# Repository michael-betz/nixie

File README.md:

# nixie
My exercise in OpenScad.
a HP 5245L frequency counter had to die for this ...

# Lessons learned the hard way
Murphy was strong on this one ...

  * Nixie pins are fragile and don't like too tight sockets. RIP 2 tubes ...
  * The HV5530 in a PQFP package has a different pinout than the one in a PLCC package. Fixed it with tons of botch wire :weary:
  * Didn't notice that the nixie tube datasheet shows the pinout from the bottom :unamused:. Fixed it with a lot more botch wire
  * Feel free to re-do the layout in kicad ...
  * Magnet wire insulation didn't hold up to 180 V. Killed 2 x ESP32 that way. Fixed it with conformal coating
  * Didn't keep conformal coating away from push buttons, it disabled them
  * Hole pattern between PCB and 3D print was off by ~ 3 mm due to a typo in the 3D model. Fixed it by bending the 3D printed part with a hot air gun
  * Had to cut some of the 3D printed stand-offs and the ESP32 PCB antenna to make it all fit

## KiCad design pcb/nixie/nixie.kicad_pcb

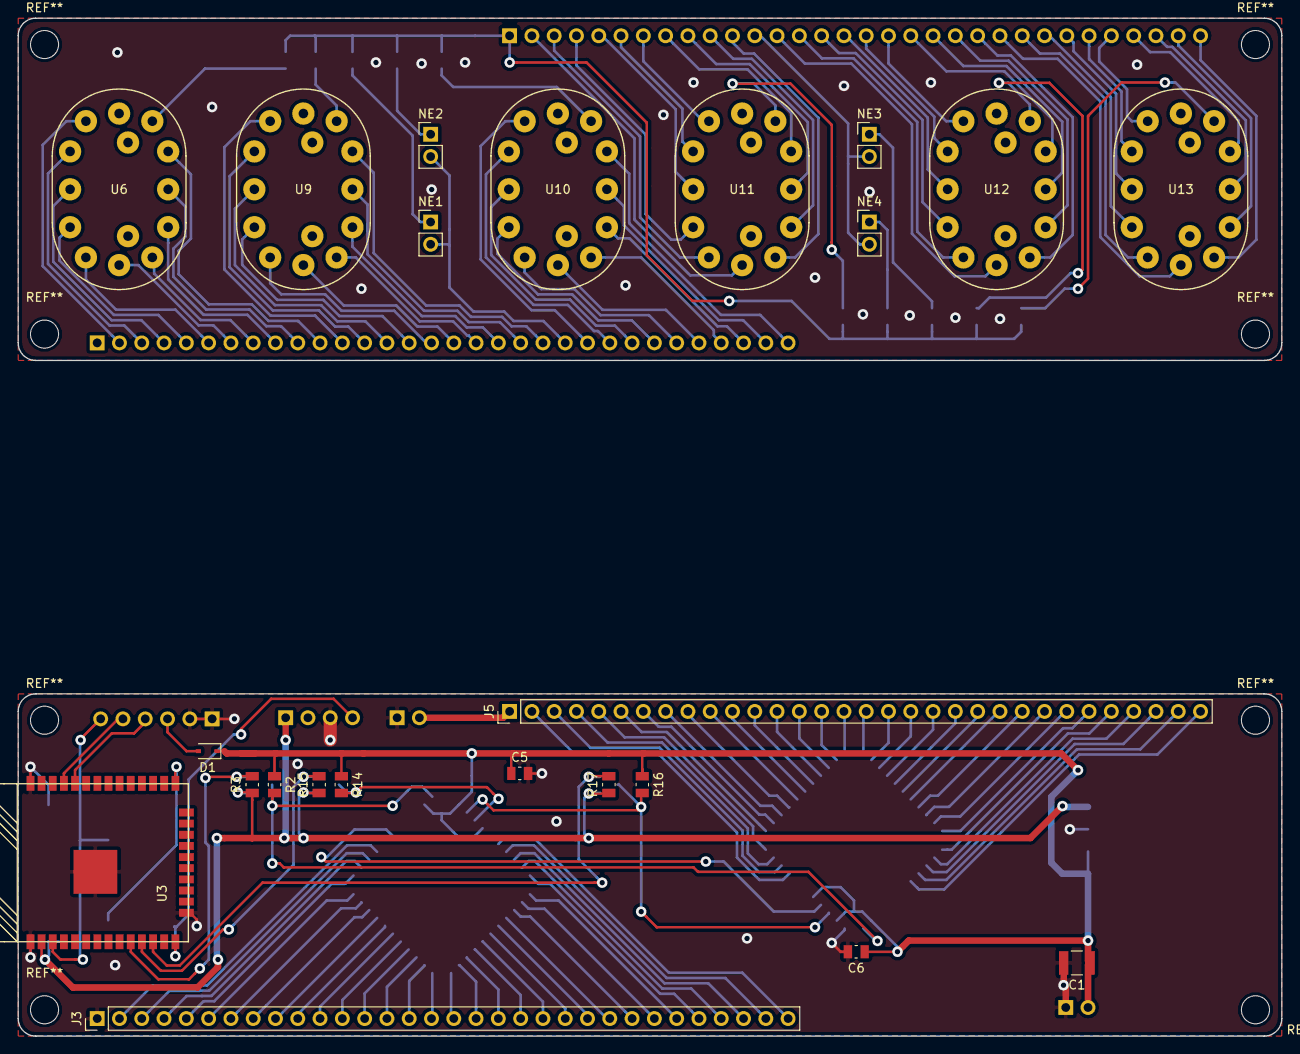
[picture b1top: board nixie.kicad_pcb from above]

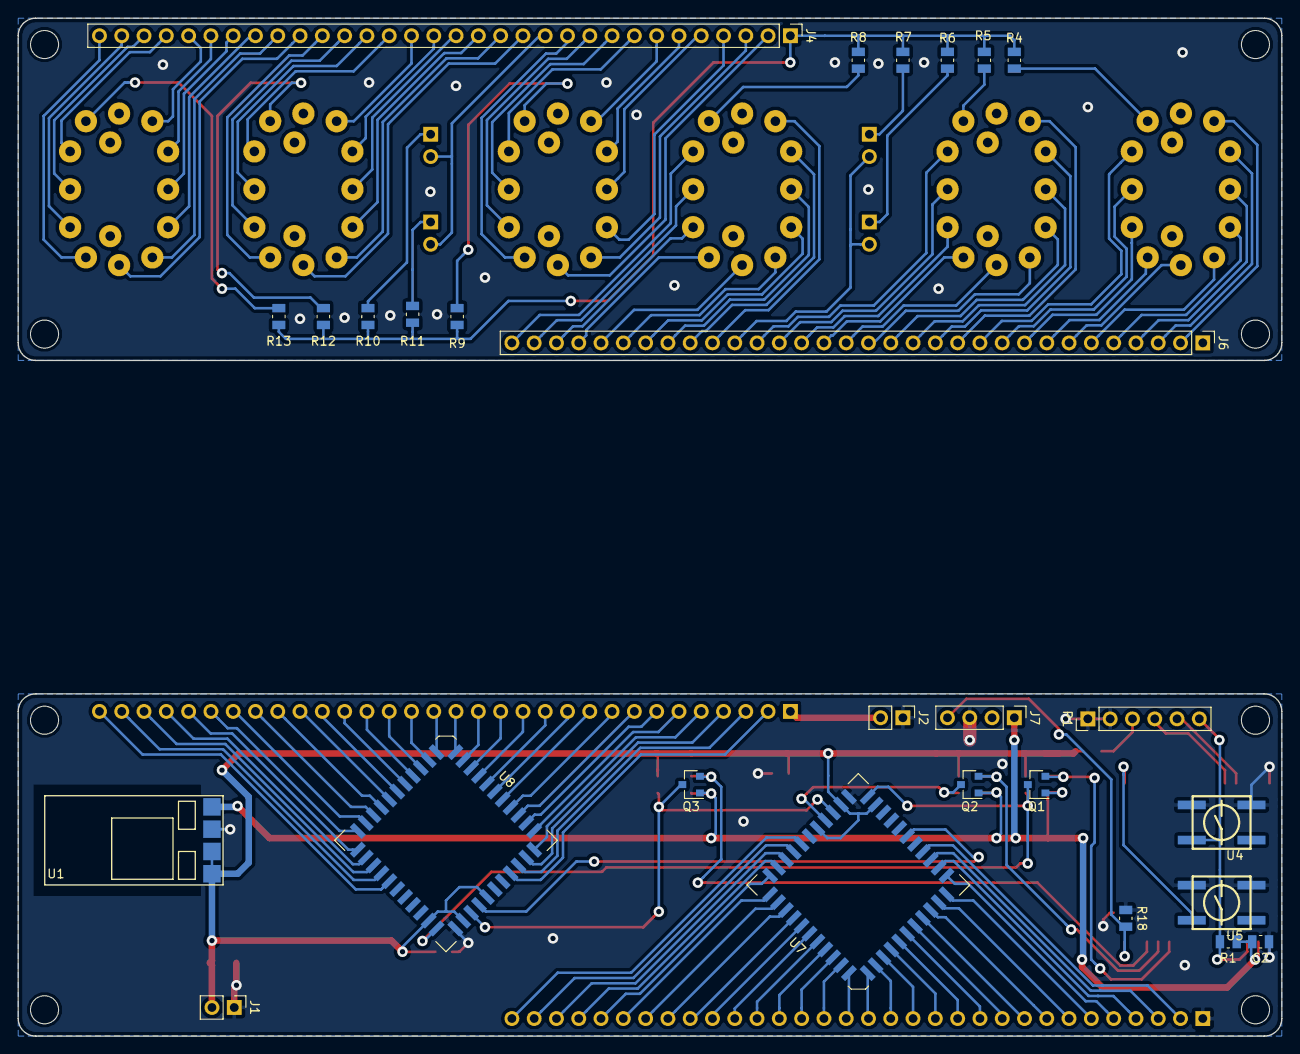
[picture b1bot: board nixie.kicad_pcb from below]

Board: 2 copper layers, 144.0 x 116.0 mm, 50 parts (27 on the bottom side), 90 nets.

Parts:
C1: 10u; C_1210_3225Metric
C2, C5, C6: 1u; C_0805_2012Metric
D1: B5819WS; D_SOD-323
J1, J2: Conn_01x02; PinHeader_1x02_P2.54mm_Vertical
J3, J4, J5, J6: Conn_01x32; PinHeader_1x32_P2.54mm_Vertical
J7: Conn_01x04; PinHeader_1x04_P2.54mm_Vertical
NE1, NE2, NE3, NE4: n; PinHeader_1x02_P2.54mm_Vertical
P1: TTL_232R_3V3; PinHeader_1x06_P2.54mm_Vertical
Q1, Q2, Q3: BSS138; SOT-23
R1: 470k; R_0805_2012Metric
R2, R3, R4, R5, R6, R7, R8, R9, R10, R11, R12, R13, R14, R15, R16, R17: 10k; R_0805_2012Metric
R18: 50R; R_0805_2012Metric
U1: DCDC_mod; ebay_dcdc
U3: ESP-WROOM-32
U4, U5: TACTILE; EVQQ2
U6, U9, U10, U11, U12, U13: nixie_8422
U7, U8: HV5530; PLCC-44

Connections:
+3V3: C2.2, J7.1, Q1.1, Q2.1, Q3.1, R1.1, R3.1, R15.1, R17.1, U1.1, U3.2
+12V: C1.1, C5.1, C6.1, D1.1, J1.2, R2.1, R14.1, R16.1, U1.3, U1.4, U7.27, U7.30, U7.33, U8.27, U8.30, U8.33
/progFlag: U3.25, U5.A, U5.A'
/rstBtn: P1.6, R1.2, U3.3, U4.A, U4.A'
/tubes/clk: Q1.3, R2.2, U7.28, U8.28
/tubes/colons_0: J5.12, J6.12, NE3.2, NE4.2, U8.2
/tubes/colons_1: J3.22, J4.22, NE1.2, NE2.2, U7.1
/tubes/dat: Q2.3, R14.2, U7.32
/tubes/n0_0: J5.29, J6.29, U8.19, U13.2
/tubes/n0_1: J5.28, J6.28, U8.18, U13.11
/tubes/n0_2: J5.27, J6.27, U8.17, U13.10
/tubes/n0_3: J5.26, J6.26, U8.16, U13.9
/tubes/n0_4: J5.25, J6.25, U8.15, U13.8
/tubes/n0_5: J5.24, J6.24, U8.14, U13.7
/tubes/n0_6: J5.23, J6.23, U8.13, U13.6
/tubes/n0_7: J5.32, J6.32, U8.22, U13.5
/tubes/n0_8: J5.31, J6.31, U8.21, U13.4
/tubes/n0_9: J5.30, J6.30, U8.20, U13.3
/tubes/n1_0: J5.19, J6.19, U8.9, U12.2
/tubes/n1_1: J5.18, J6.18, U8.8, U12.11
/tubes/n1_2: J5.17, J6.17, U8.7, U12.10
/tubes/n1_3: J5.16, J6.16, U8.6, U12.9
/tubes/n1_4: J5.15, J6.15, U8.5, U12.8
/tubes/n1_5: J5.14, J6.14, U8.4, U12.7
/tubes/n1_6: J5.13, J6.13, U8.3, U12.6
/tubes/n1_7: J5.22, J6.22, U8.12, U12.5
/tubes/n1_8: J5.21, J6.21, U8.11, U12.4
/tubes/n1_9: J5.20, J6.20, U8.10, U12.3
/tubes/n2_0: J5.8, J6.8, U8.42, U11.2
/tubes/n2_1: J5.7, J6.7, U8.41, U11.11
/tubes/n2_2: J5.6, J6.6, U8.40, U11.10
/tubes/n2_3: J5.5, J6.5, U8.39, U11.9
/tubes/n2_4: J5.4, J6.4, U8.38, U11.8
/tubes/n2_5: J5.3, J6.3, U8.37, U11.7
/tubes/n2_6: J5.2, J6.2, U8.36, U11.6
/tubes/n2_7: J5.11, J6.11, U8.1, U11.5
/tubes/n2_8: J5.10, J6.10, U8.44, U11.4
/tubes/n2_9: J5.9, J6.9, U8.43, U11.3
/tubes/n3_0: J3.32, J4.32, U7.35, U10.2
/tubes/n3_1: J3.23, J4.23, U7.44, U10.11
/tubes/n3_2: J3.24, J4.24, U7.43, U10.10
/tubes/n3_3: J3.25, J4.25, U7.42, U10.9
/tubes/n3_4: J3.26, J4.26, U7.41, U10.8
/tubes/n3_5: J3.27, J4.27, U7.40, U10.7
/tubes/n3_6: J3.28, J4.28, U7.39, U10.6
/tubes/n3_7: J3.29, J4.29, U7.38, U10.5
/tubes/n3_8: J3.30, J4.30, U7.37, U10.4
/tubes/n3_9: J3.31, J4.31, U7.36, U10.3
/tubes/n4_0: J3.21, J4.21, U7.2, U9.2
/tubes/n4_1: J3.12, J4.12, U7.11, U9.11
/tubes/n4_2: J3.13, J4.13, U7.10, U9.10
/tubes/n4_3: J3.14, J4.14, U7.9, U9.9
/tubes/n4_4: J3.15, J4.15, U7.8, U9.8
/tubes/n4_5: J3.16, J4.16, U7.7, U9.7
/tubes/n4_6: J3.17, J4.17, U7.6, U9.6
/tubes/n4_7: J3.18, J4.18, U7.5, U9.5
/tubes/n4_8: J3.19, J4.19, U7.4, U9.4
/tubes/n4_9: J3.20, J4.20, U7.3, U9.3
/tubes/n5_0: J3.11, J4.11, U6.2, U7.12
/tubes/n5_1: J3.2, J4.2, U6.11, U7.21
/tubes/n5_2: J3.3, J4.3, U6.10, U7.20
/tubes/n5_3: J3.4, J4.4, U6.9, U7.19
/tubes/n5_4: J3.5, J4.5, U6.8, U7.18
/tubes/n5_5: J3.6, J4.6, U6.7, U7.17
/tubes/n5_6: J3.7, J4.7, U6.6, U7.16
/tubes/n5_7: J3.8, J4.8, U6.5, U7.15
/tubes/n5_8: J3.9, J4.9, U6.4, U7.14
/tubes/n5_9: J3.10, J4.10, U6.3, U7.13
/tubes/nLatch: Q3.3, R16.2, U7.31, U8.31
GND: C1.2, C2.1, C5.2, C6.2, J1.1, J2.1, J3.1, J4.1, J7.3, P1.1, P1.2, R18.1, U1.2, U3.1, U3.15, U3.38, U3.39, U4.B, U4.B', U5.B, U5.B', U7.29, U8.29
HT: J2.2, J5.1, J6.1, R4.2, R5.1, R6.1, R7.1, R8.1, R9.1, R10.1, R11.1, R12.1, R13.1
unnamed: D1.2, P1.3
unnamed: J7.2, U3.13
unnamed: J7.4, R18.2, U3.14
unnamed: NE1.1, R6.2
unnamed: NE2.1, R7.2
unnamed: NE3.1, R10.2
unnamed: NE4.1, R11.2
unnamed: P1.4, U3.34
unnamed: P1.5, U3.35
unnamed: Q1.2, R3.2, U3.10
unnamed: Q2.2, R15.2, U3.11
unnamed: Q3.2, R17.2, U3.12
unnamed: R4.1, U6.1
unnamed: R5.2, U9.1
unnamed: R8.2, U10.1
unnamed: R9.2, U11.1
unnamed: R12.2, U12.1
unnamed: R13.2, U13.1
unnamed: U7.23, U8.32

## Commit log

2018-04-16 The vision
2018-04-20 case work
2018-05-07 Not sure where im going here
2018-05-14 PCB work
2018-05-18 Added MCP1630 idea
2018-05-20 tricky
2018-05-20 rendered top
2018-05-20 larger lid
2018-05-21 done, done done done
2018-05-22 added finished frontpanel
2018-05-23 Finished lower part
2018-05-24 Decided for 12V input voltage
2018-05-24 Major cleanup.
    Split 3 parts into 3 modules for separate printing.
    Fix Mounting holes for PCB behind frontpanel,
    which were off by 1 mm each.
    Increase Z-depth of teeth slots (x1.5).
    Remove outdated pictures and stl files
2018-05-25 Technically done
2018-05-30 Minor imprpvements
2018-07-11 Initial
2018-07-12 Wrong pinout on HV5530 :(
2018-07-17 Test pattern works
2018-07-18 Shows time
2018-07-18 seconds
2018-07-21 Docs
2018-07-21 added 3D pic
2020-04-18 remove settings.json
2021-06-07 make it a platformio project
    * use esp-comms to bring up wifi, manage settings in a .json and run the web-interface
